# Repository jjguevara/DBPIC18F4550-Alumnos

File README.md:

# DBPIC18F4550-Alumnos
1. Archivos fuente para placa de desarrollo PIC18F4550 de alumnos

2. HIDBootloader.exe, es el programa gestor del bootloader, compatible con Windows 7/8/8.1/10, requiere de .NET Framework 3.5.
En la siguiente página, se muestra un ejemplo de utilización del programa:http://rado.heliohost.org/content_5.htm

3. USB Device - HID - HID Bootloader - C18 - PIC18F4550.hex, es el programa bootloader que debe cargarse en la memoria de programa del microcontrolador usando un programador externo, la placa de desarrollo dispone de un puerto ICSP para este propósito. Programadores compatibles: Pickit 2/3 y Brenner 8.

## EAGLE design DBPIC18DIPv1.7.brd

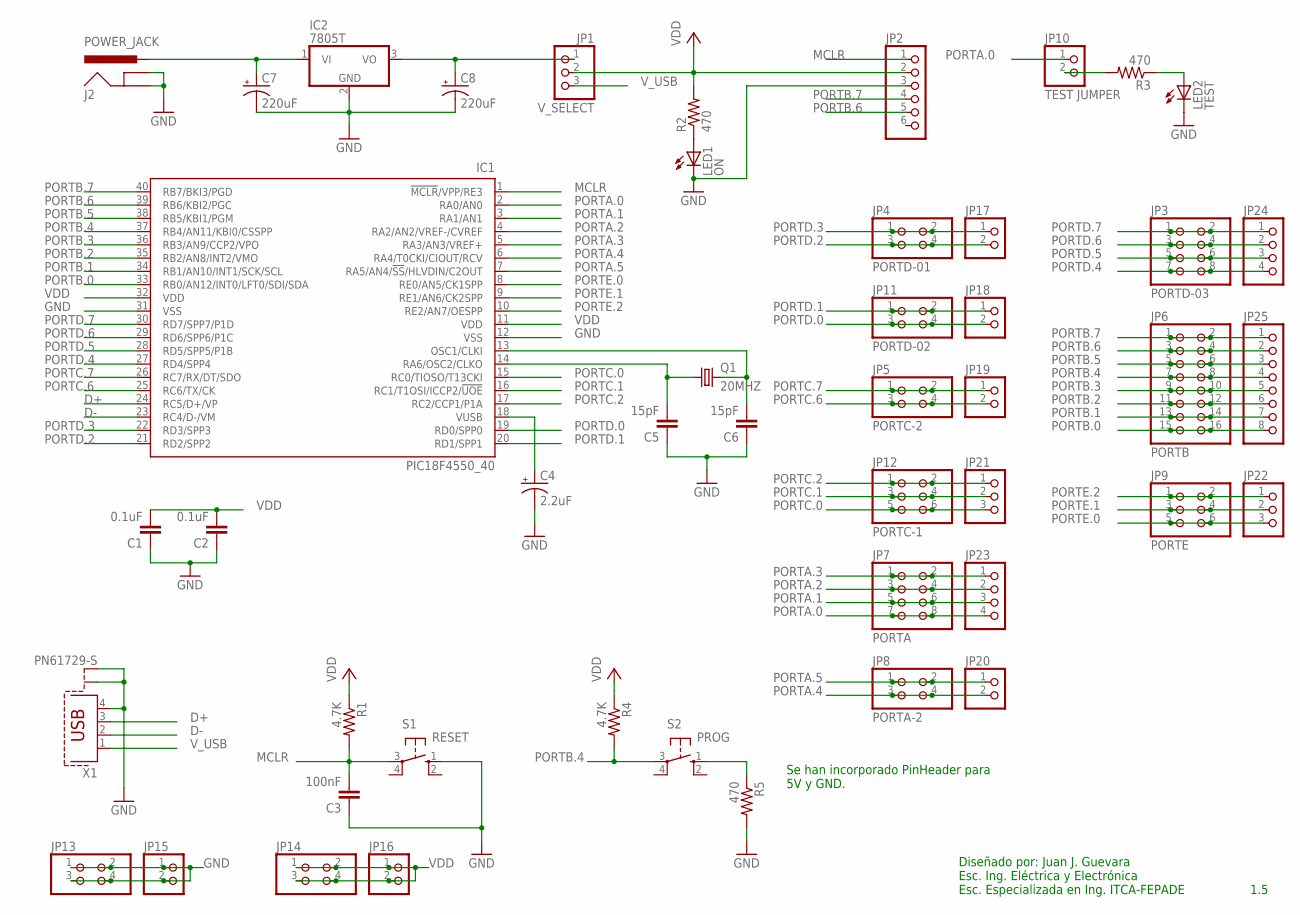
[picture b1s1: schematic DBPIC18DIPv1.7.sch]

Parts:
C1, C2: 0.1uF; C2.5-2
C3: 100nF; C2.5-2
C4: 2.2uF; E1,8-4
C5, C6: 15pF; C2.5-2
C7: 220uF; E2-5
C8: 220uF; E1,8-4
IC1: PIC18F4550_40; DIL40
IC2: 7805T; TO220H
J2: POWER_JACK; POWER_JACK_PTH
JP1: V_SELECT; 1X03
JP2: PINHD-1X6; 1X06
JP3: PORTD-03; 2X04
JP4: PORTD-01; 2X02
JP5: PORTC-2; 2X02
JP6: PORTB; 2X08
JP7: PORTA; 2X04
JP8: PORTA-2; 2X02
JP9: PORTE; 2X03
JP10: TEST JUMPER; 1X02
JP11: PORTD-02; 2X02
JP12: PORTC-1; 2X03
JP13, JP14: PINHD-2X2; 2X02
JP15, JP16, JP17, JP18, JP19, JP20: PINHD-1X2; 1X02
JP21, JP22: PINHD-1X3; 1X03
JP23, JP24: PINHD-1X4; 1X04
JP25: PINHD-1X8; 1X08
LED1: ON; LED3MM
LED2: TEST; LED3MM
Q1: 20MHZ; HC49/S
R1, R4: 4.7K; 0207/12
R2, R3, R5: 470; 0207/12
S1: RESET; B3F-10XX
S2: PROG; B3F-10XX
X1: PN61729-S

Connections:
D+: IC1.24 (RC5/D+/VP), X1.3
D-: IC1.23 (RC4/D-/VM), X1.2
GND: C1.1, C2.1, C3.1, C4.-, C5.1, C6.1, C7.-, C8.-, IC1.12 (VSS), IC1.31 (VSS), IC2.2 (GND), J2.GND, J2.GNDBREAK, JP2.3, JP13.1, JP13.2, JP13.3, JP13.4, JP15.1, JP15.2, LED1.K (C), LED2.K (C), R5.2, S1.1 (S), X1.4, X1.S1, X1.S2
MCLR: C3.2, IC1.1 (!MCLR!/VPP/RE3), JP2.1, R1.2, S1.3
unnamed: LED2.A, R3.1
unnamed: C6.2, IC1.13 (OSC1/CLKI), Q1.2
unnamed: C5.2, IC1.14 (RA6/OSC2/CLKO), Q1.1
unnamed: C4.+, IC1.18 (VUSB)
unnamed: C8.+, IC2.3 (VO), JP1.1
unnamed: LED1.A, R2.1
unnamed: JP10.2, R3.2
unnamed: R5.1, S2.1 (S)
unnamed: C7.+, IC2.1 (VI), J2.PWR
PORTA.0: IC1.2 (RA0/AN0), JP7.7, JP7.8, JP10.1, JP23.4
PORTA.1: IC1.3 (RA1/AN1), JP7.5, JP7.6, JP23.3
PORTA.2: IC1.4 (RA2/AN2/VREF-/CVREF), JP7.3, JP7.4, JP23.2
PORTA.3: IC1.5 (RA3/AN3/VREF+), JP7.1, JP7.2, JP23.1
PORTA.4: IC1.6 (RA4/T0CKI/CIOUT/RCV), JP8.3, JP8.4, JP20.2
PORTA.5: IC1.7 (RA5/AN4/!SS!/HLVDIN/C2OUT), JP8.1, JP8.2, JP20.1
PORTB.0: IC1.33 (RB0/AN12/INT0/LFT0/SDI/SDA), JP6.15, JP6.16, JP25.8
PORTB.1: IC1.34 (RB1/AN10/INT1/SCK/SCL), JP6.13, JP6.14, JP25.7
PORTB.2: IC1.35 (RB2/AN8/INT2/VMO), JP6.11, JP6.12, JP25.6
PORTB.3: IC1.36 (RB3/AN9/CCP2/VPO), JP6.9, JP6.10, JP25.5
PORTB.4: IC1.37 (RB4/AN11/KBI0/CSSPP), JP6.7, JP6.8, JP25.4, R4.2, S2.3
PORTB.5: IC1.38 (RB5/KBI1/PGM), JP6.5, JP6.6, JP25.3
PORTB.6: IC1.39 (RB6/KBI2/PGC), JP2.5, JP6.3, JP6.4, JP25.2
PORTB.7: IC1.40 (RB7/BKI3/PGD), JP2.4, JP6.1, JP6.2, JP25.1
PORTC.0: IC1.15 (RC0/TIOSO/T13CKI), JP12.5, JP12.6, JP21.3
PORTC.1: IC1.16 (RC1/T1OSI/ICCP2/!UOE), JP12.3, JP12.4, JP21.2
PORTC.2: IC1.17 (RC2/CCP1/P1A), JP12.1, JP12.2, JP21.1
PORTC.6: IC1.25 (RC6/TX/CK), JP5.3, JP5.4, JP19.2
PORTC.7: IC1.26 (RC7/RX/DT/SDO), JP5.1, JP5.2, JP19.1
PORTD.0: IC1.19 (RD0/SPP0), JP11.3, JP11.4, JP18.2
PORTD.1: IC1.20 (RD1/SPP1), JP11.1, JP11.2, JP18.1
PORTD.2: IC1.21 (RD2/SPP2), JP4.3, JP4.4, JP17.2
PORTD.3: IC1.22 (RD3/SPP3), JP4.1, JP4.2, JP17.1
PORTD.4: IC1.27 (RD4/SPP4), JP3.7, JP3.8, JP24.4
PORTD.5: IC1.28 (RD5/SPP5/P1B), JP3.5, JP3.6, JP24.3
PORTD.6: IC1.29 (RD6/SPP6/P1C), JP3.3, JP3.4, JP24.2
PORTD.7: IC1.30 (RD7/SPP7/P1D), JP3.1, JP3.2, JP24.1
PORTE.0: IC1.8 (RE0/AN5/CK1SPP), JP9.5, JP9.6, JP22.3
PORTE.1: IC1.9 (RE1/AN6/CK2SPP), JP9.3, JP9.4, JP22.2
PORTE.2: IC1.10 (RE2/AN7/OESPP), JP9.1, JP9.2, JP22.1
VDD: C1.2, C2.2, IC1.11 (VDD), IC1.32 (VDD), JP1.2, JP2.2, JP14.1, JP14.2, JP14.3, JP14.4, JP16.1, JP16.2, R1.1, R2.2, R4.1
V_USB: JP1.3, X1.1

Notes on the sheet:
Diseñado por: Juan J. Guevara Esc. Ing. Eléctrica y Electrónica Esc. Especializada en Ing. ITCA-FEPADE
1.5
Se han incorporado PinHeader para 5V y GND.

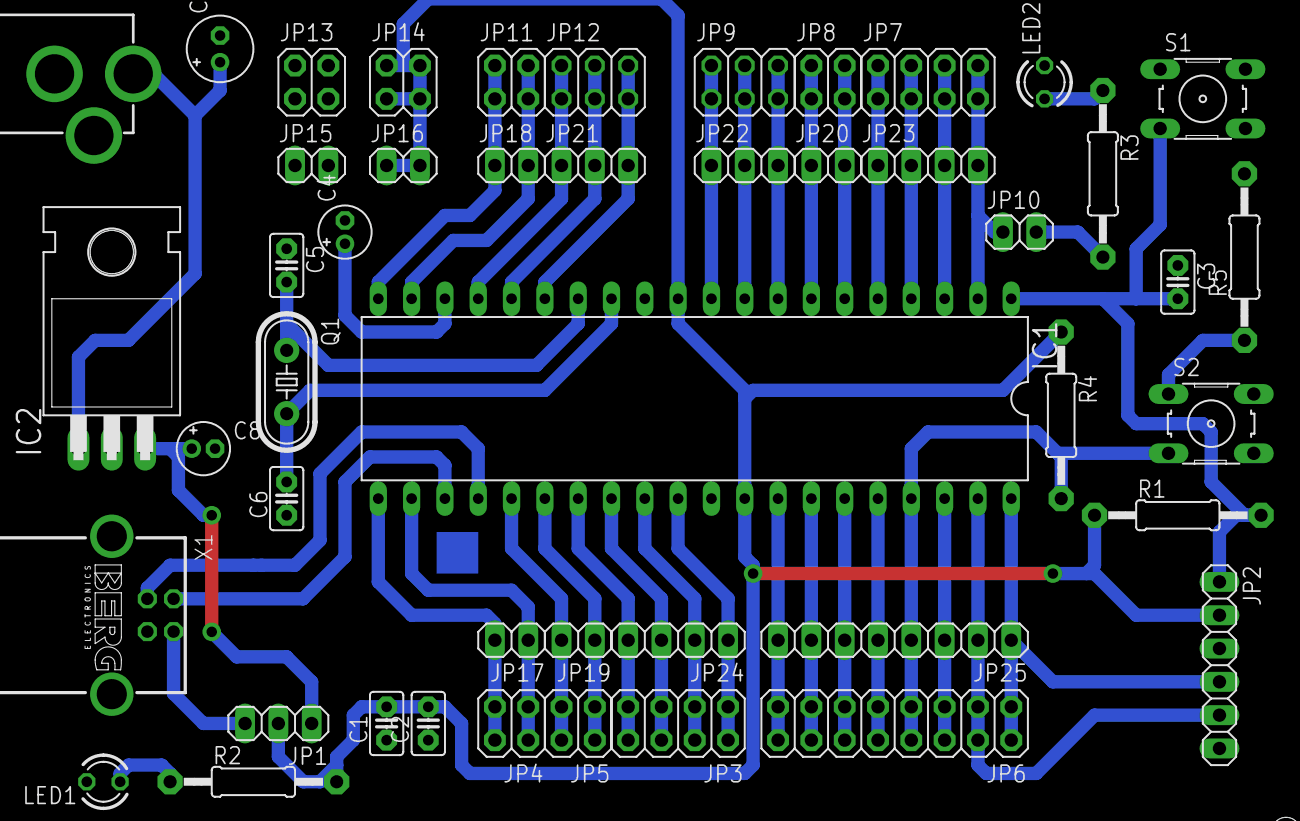
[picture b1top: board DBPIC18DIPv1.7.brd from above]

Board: 2 copper layers, 47 parts (0 on the bottom side), 45 nets.

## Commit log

2018-07-12 Versión 1.7
    1. Se ha incorporado un resistor a RB4 para protegerlo durante la activación del botón PROG

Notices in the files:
parts and their libraries:
SparkFun-Connectors: Licensing: Creative Commons ShareAlike 4.0 International - https://creativecommons.org/licenses/by-sa/4.0
